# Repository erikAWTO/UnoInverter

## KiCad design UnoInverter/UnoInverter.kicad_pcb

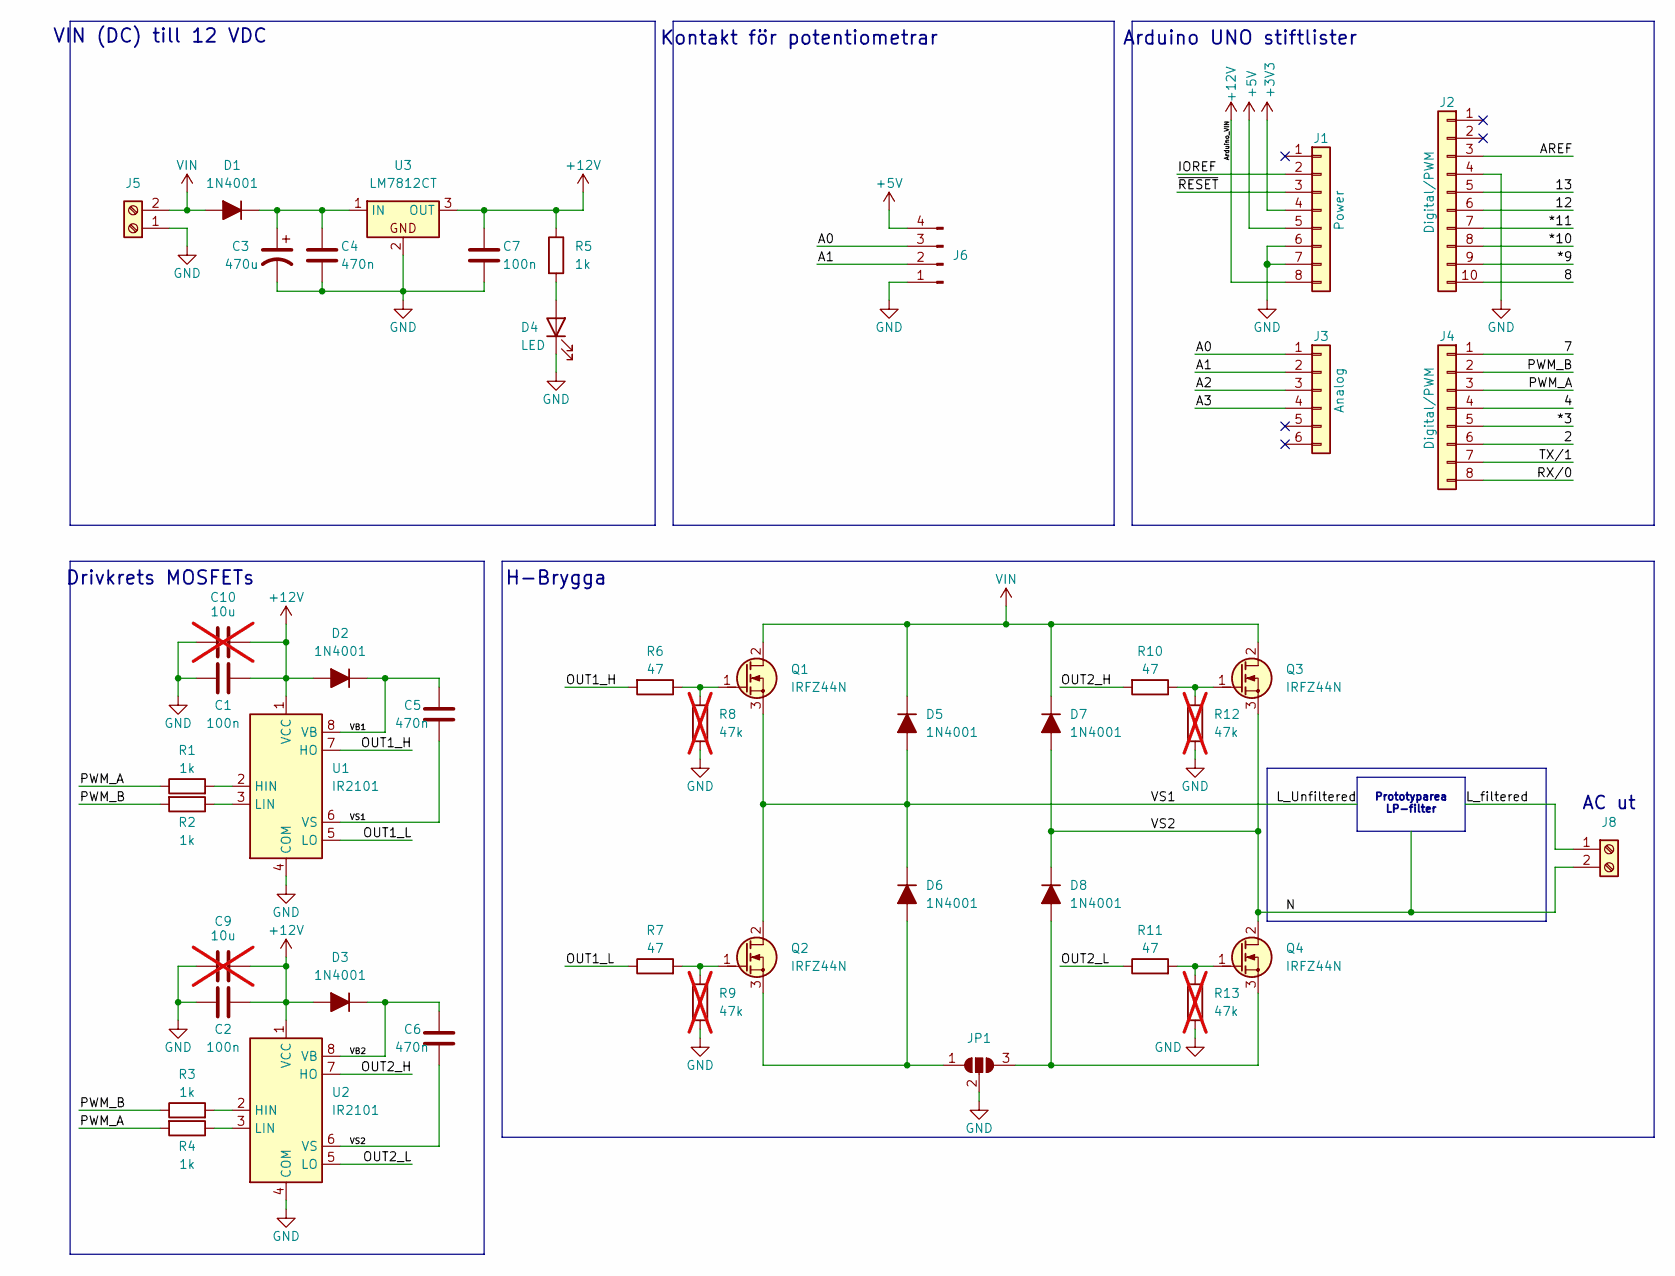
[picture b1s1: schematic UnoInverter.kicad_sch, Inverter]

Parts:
C1, C2, C7: 100n; C_0805_2012Metric_Pad1.18x1.45mm_HandSolder
C3: 470u; CP_Radial_D10.0mm_P5.00mm
C4, C5, C6: 470n; C_0805_2012Metric_Pad1.18x1.45mm_HandSolder
C9, C10: 10u; C_0805_2012Metric_Pad1.18x1.45mm_HandSolder; not fitted
D1, D2, D3, D5, D6, D7, D8: 1N4001; D_DO-41_SOD81_P7.62mm_Horizontal
D4: LED; LED_D5.0mm_Horizontal_O1.27mm_Z15.0mm
J1: Power; PinHeader_1x08_P2.54mm_Vertical
J2: Digital/PWM; PinHeader_1x10_P2.54mm_Vertical
J3: Analog; PinHeader_1x06_P2.54mm_Vertical
J4: Digital/PWM; PinHeader_1x08_P2.54mm_Vertical
J5, J8: Screw_Terminal_01x02; TerminalBlock_Phoenix_PT-1,5-2-5.0-H_1x02_P5.00mm_Horizontal
J6: Conn_01x04_Pin; PinHeader_1x04_P2.54mm_Vertical
JP1: SolderJumper_3_Open; SolderJumper-3_P2.0mm_Open_TrianglePad1.0x1.5mm
Q1, Q2, Q3, Q4: IRFZ44N; TO-220-3_Vertical_GDS
R1, R2, R3, R4, R5: 1k; R_0805_2012Metric_Pad1.20x1.40mm_HandSolder
R6, R7, R10, R11: 47; R_0805_2012Metric_Pad1.20x1.40mm_HandSolder
R8, R9, R12, R13: 47k; R_0805_2012Metric_Pad1.20x1.40mm_HandSolder; not fitted
U1, U2: IR2101; SOIC-8_3.9x4.9mm_P1.27mm
U3: LM7812CT; TO-220-3_Vertical

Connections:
+3V3: J1.4
+5V: J1.5, J6.4
+12V: C1.2, C2.2, C7.1, C9.2, C10.2, D2.2 (A), D3.2 (A), J1.8, R5.1, U1.1 (VCC), U2.1 (VCC), U3.3 (OUT)
/2: J4.6
/4: J4.4
/7: J4.1
/8: J2.10
/12: J2.6
/13: J2.5
/ L_filtered: J8.1
/*3: J4.5
/*9: J2.9
/*10: J2.8
/*11: J2.7
/A0: J3.1, J6.3
/A1: J3.2, J6.2
/A2: J3.3
/A3: J3.4
/AREF: J2.3
/IOREF: J1.2
/OUT1_H: R6.2, U1.7 (HO)
/OUT1_L: R7.1, U1.5 (LO)
/OUT2_H: R10.2, U2.7 (HO)
/OUT2_L: R11.1, U2.5 (LO)
/PWM_A: J4.3, R1.1, R4.2
/PWM_B: J4.2, R2.2, R3.1
/RX/0: J4.8
/TX/1: J4.7
/VB1: C5.1, D2.1 (K), U1.8 (VB)
/VB2: C6.1, D3.1 (K), U2.8 (VB)
/~RESET: J1.3
GND: C1.1, C2.1, C3.2, C4.2, C7.2, C9.1, C10.1, D4.1 (K), J1.6, J1.7, J2.4, J5.1, J6.1, JP1.2 (C), R8.1, R9.2, R12.2, R13.1, U1.4 (COM), U2.4 (COM), U3.2
unnamed: C3.1, C4.1, D1.1 (K), U3.1 (IN)
unnamed: D4.2 (A), R5.2
unnamed: D6.2 (A), JP1.1 (A), Q2.3 (S)
unnamed: D8.2 (A), JP1.3 (B), Q4.3 (S)
unnamed: Q1.1 (G), R6.1, R8.2
unnamed: Q2.1 (G), R7.2, R9.1
unnamed: Q3.1 (G), R10.1, R12.1
unnamed: Q4.1 (G), R11.2, R13.2
unnamed: R1.2, U1.2 (HIN)
unnamed: R2.1, U1.3 (LIN)
unnamed: R3.2, U2.2 (HIN)
unnamed: R4.1, U2.3 (LIN)
VIN: D1.2 (A), D5.1 (K), D7.1 (K), J5.2, Q1.2 (D), Q3.2 (D)

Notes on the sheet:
Prototyparea LP-filter
AC ut
Drivkrets MOSFETs
VIN (DC) till 12 VDC
H-Brygga
Kontakt för potentiometrar
Arduino UNO stiftlister

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
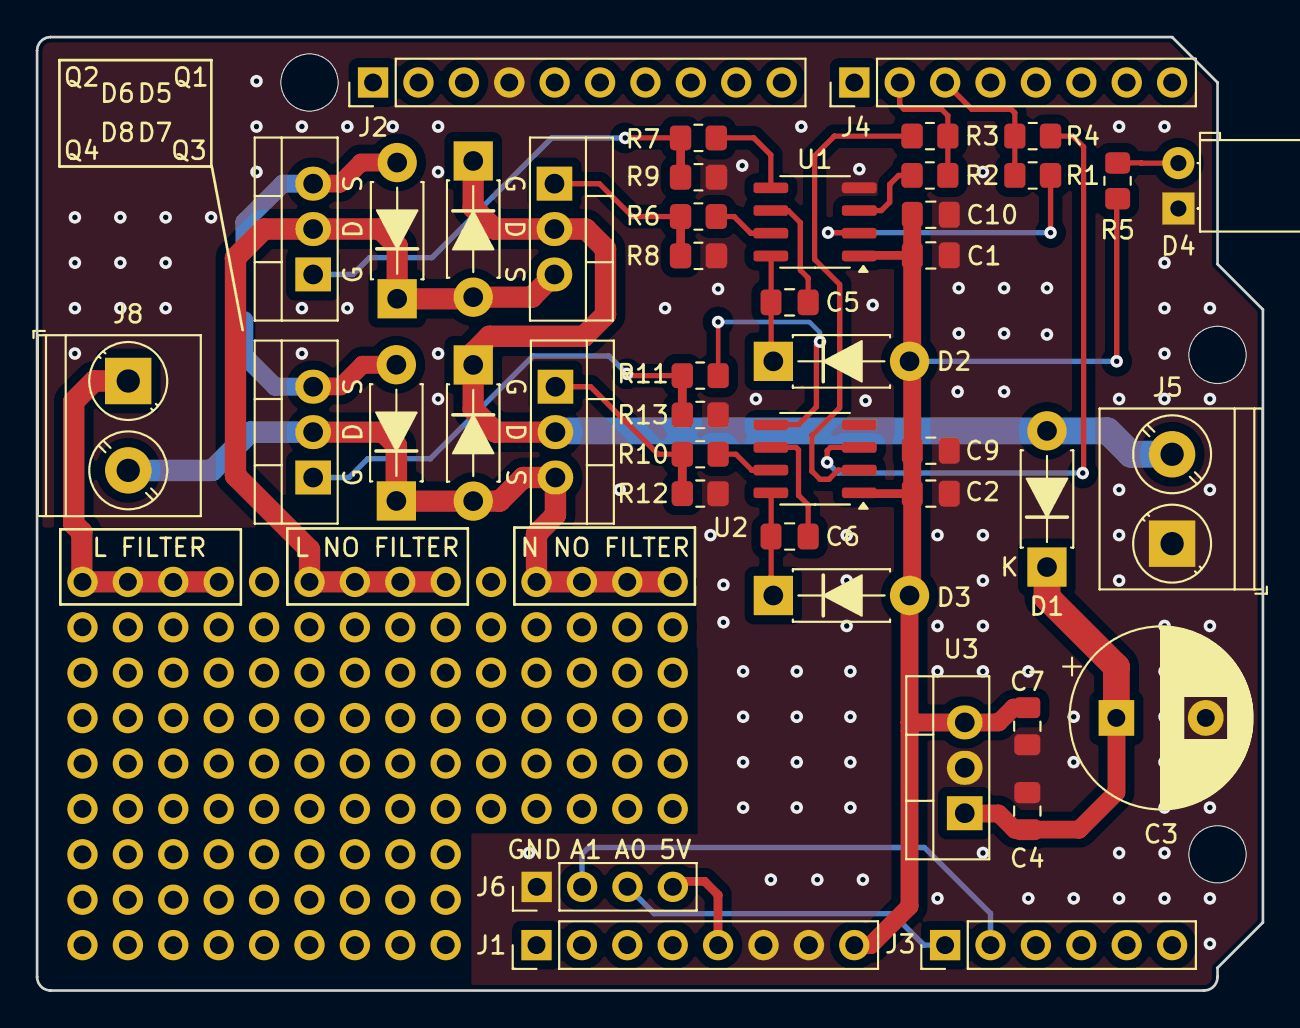
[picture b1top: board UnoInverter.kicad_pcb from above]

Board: 2 copper layers, 68.6 x 53.3 mm, 77 parts (1 on the bottom side), 30 nets.

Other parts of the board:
15, 16, 17, 18, 19, 20, 21, 22, 23, 24, 25, 26, 27, 28, 29, 30, 31, 32, 33, 34, 35, 36, 37, 38, 39, 40, 41, 42, 43: (no value)
MH1, MH3, MH4: MountingHole_3.2mm

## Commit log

2025-01-23 Added KiCad files
2025-01-23 Added pdf schematic
2025-01-23 Added untested firmware for pins 5 and 6
